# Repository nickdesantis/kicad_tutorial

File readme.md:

# PCB Tutorial
This repo is to support a tutorial in which we'll learn how to make our own printed circuit boards (PCBs) with Kicad by laying out a simple audio amplifier.

## Goals
While we'll be using Kicad, all of the skills we'll be learning are transferrable to other EDA packages:
* Schematic capture
* Board layout
* Part creation and libraries
* Producing outputs for production

## Motivation
Why make our own PCBs?
* When you want more than one of something
* Better signal intengrity
* Breadboarding gets unmanagable pretty quickly
* It's cheap!
* More parts! Through hole packages are becoming rarer and rarer - for the cost of one breakout board, you could do 2 or 3 PCB spins!

## Prerequisites
* It's best if you can bring your own laptop
* [Download and Install Kicad](http://kicad-pcb.org/)
* Bring a mouse
* Some knowledge of circuits would be handy

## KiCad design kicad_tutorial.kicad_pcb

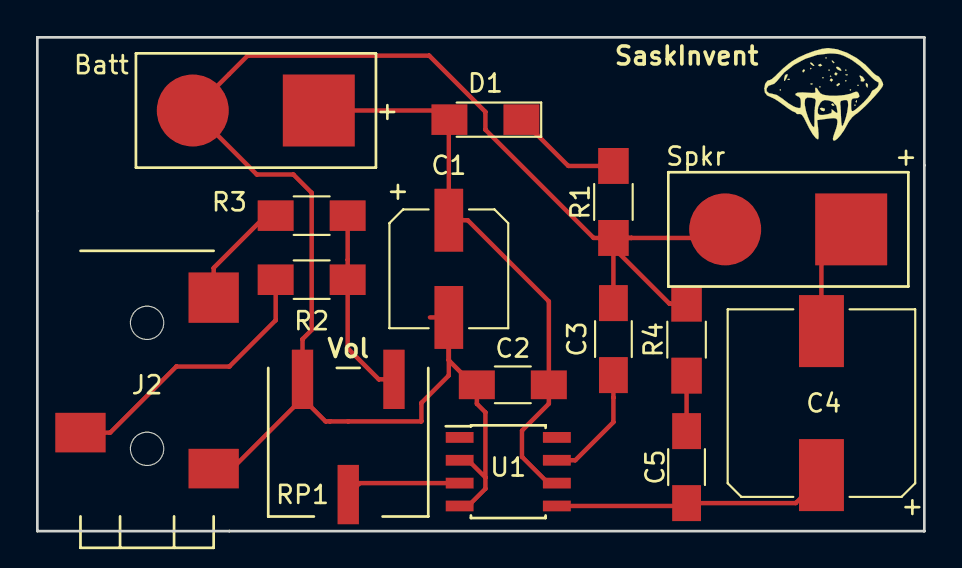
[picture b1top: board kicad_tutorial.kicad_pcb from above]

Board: 2 copper layers, 49.3 x 27.4 mm, 15 parts (0 on the bottom side), 11 nets.

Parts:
C1: 100uF; CP_Elec_6.3x7.7
C2, C3: 0.1uF; C_1206_HandSoldering
C4: 1000uF; CP_Elec_10x10
C5: 0.047uF; C_1206_HandSoldering
D1: LED; LED_1206_HandSoldering
J1: Batt; solder_pads_2
J2: 3.5mm Audio; audio_jack_cui_sj3523
J3: Spkr; solder_pads_2
R1: 270; R_1206_HandSoldering
R2, R3: 1k; R_1206_HandSoldering
R4: 10; R_1206_HandSoldering
RP1: POT_TRIM; trimpot_bourns_3361P
U1: LM386; SOIC-8_3.9x4.9mm_Pitch1.27mm

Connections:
+9V: C1.1, C2.1, D1.2, J1.1, U1.6
GND: C1.2, C2.2, C3.1, J1.2, J2.1, J3.2, R1.1, R4.2, RP1.3, U1.2, U1.4
unnamed: C3.2, U1.7
unnamed: C4.1, C5.1, U1.5
unnamed: C4.2, J3.1
unnamed: C5.2, R4.1
unnamed: D1.1, R1.2
unnamed: J2.2, R3.2
unnamed: J2.3, R2.2
unnamed: R2.1, R3.1, RP1.1
unnamed: RP1.2, U1.3

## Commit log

2018-01-09 Added LM386 datasheet
2018-01-09 Added Volumne pot and audio jack data sheets
2018-01-10 Added speaker and LED data sheets
2018-01-11 Initial wiring up of amp circuit with existing library components. Fixed sheet size to 8.5x11
2018-01-12 Switched pot with trimmer. Project and Sch updates. Added BOM.
2018-01-12 Switched audio jack to better supplier w/ superior documentation. Updated BOM accordingly.
2018-01-12 Moved project lib to project folder. Added Audio Jack. Annotated Schematic. Schematic now passes ERC
2018-01-12 Associated footprints to majority of components
2018-01-12 Updated BOM
2018-01-13 Added trimpot fp & 3d
2018-01-13 Associated trimpot fp
2018-01-13 added solder pad fp
2018-01-13 Added audio jack fp & 3d
2018-01-13 Completed layout. Some fp changes.
2018-01-13 Added render to readme
2018-01-13 Fixed render img - no axis or gridlines now
2018-01-13 Added schematic image
2018-01-13 Started working on slides
2018-01-13 Created fabrication folder
